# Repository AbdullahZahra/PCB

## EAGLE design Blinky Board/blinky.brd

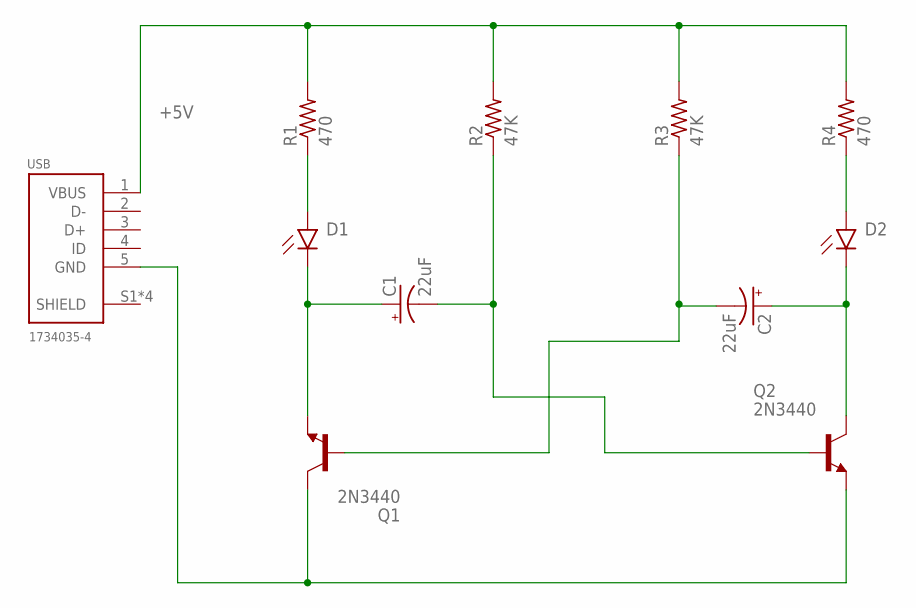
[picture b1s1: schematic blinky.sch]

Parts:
C1, C2: 22uF; B45181A
D1: CHIP-FLAT-R_1206; LEDC3216X75N_FLAT-R
D2: CHIP-FLAT-G_1206; LEDC3216X75N_FLAT-G
Q1, Q2: 2N3440; TO5
R1, R4: 470; 0204/7
R2, R3: 47K; 0204/7
USB: 1734035-4

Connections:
+5V: R1.2, R2.2, R3.2, R4.2, USB.1 (VBUS)
unnamed: D1.A, R1.1
unnamed: D2.A, R4.1
unnamed: C1.+, D1.C, Q1.1 (E)
unnamed: C1.-, Q2.2 (B), R2.1
unnamed: C2.+, D2.C, Q2.3 (C)
unnamed: C2.-, Q1.2 (B), R3.1
unnamed: Q1.3 (C), Q2.1 (E), USB.5 (GND)
SHIELD: USB.S1 (SHIELD), USB.S2 (SHIELD), USB.S3 (SHIELD), USB.S4 (SHIELD)

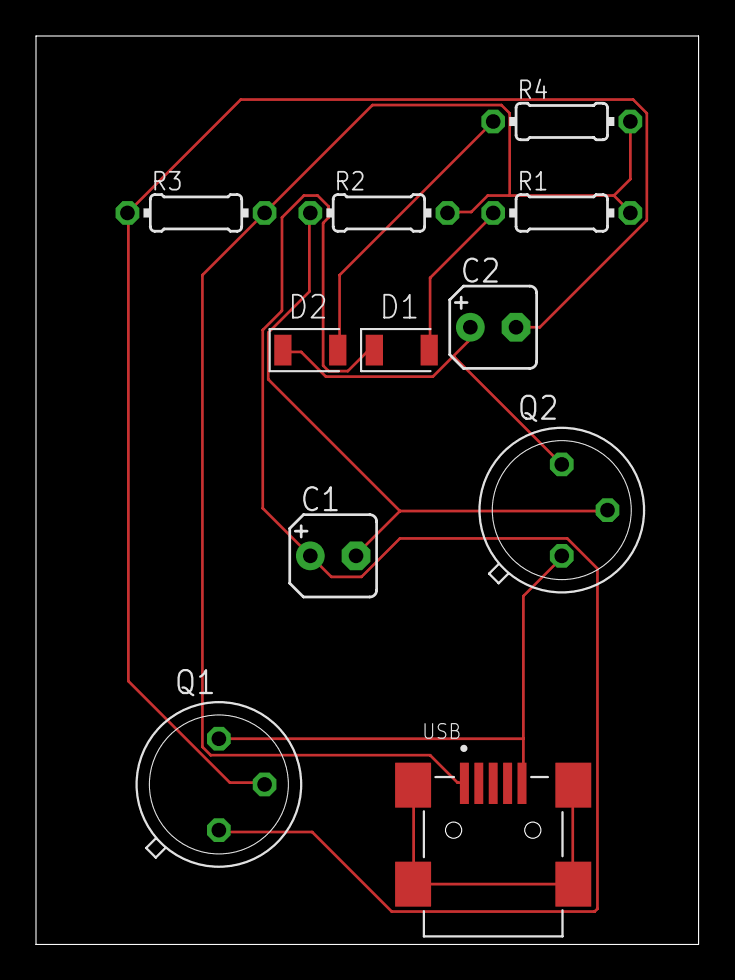
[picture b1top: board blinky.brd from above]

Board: 2 copper layers, 36.8 x 50.5 mm, 11 parts (0 on the bottom side), 9 nets.
